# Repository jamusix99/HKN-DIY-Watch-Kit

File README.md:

# HKN Beta Psi DIY Watch Project
By: John Mentgen \
Init Date: 2026-02-16

## Directory Setup
 - **HW Design**: KiCad files for board setup
 - **SW**: Software Repo with details on how to compile

## Project Purpose
This project is meant to provide new ECEN students with a fun soldering project that members of IEEE and HKN Beta-Psi can help with and talk to students about possibilities in this field. The file holding the BOM details rough cost estimates for buying new parts from DigiKey and boards from JLCPCB.

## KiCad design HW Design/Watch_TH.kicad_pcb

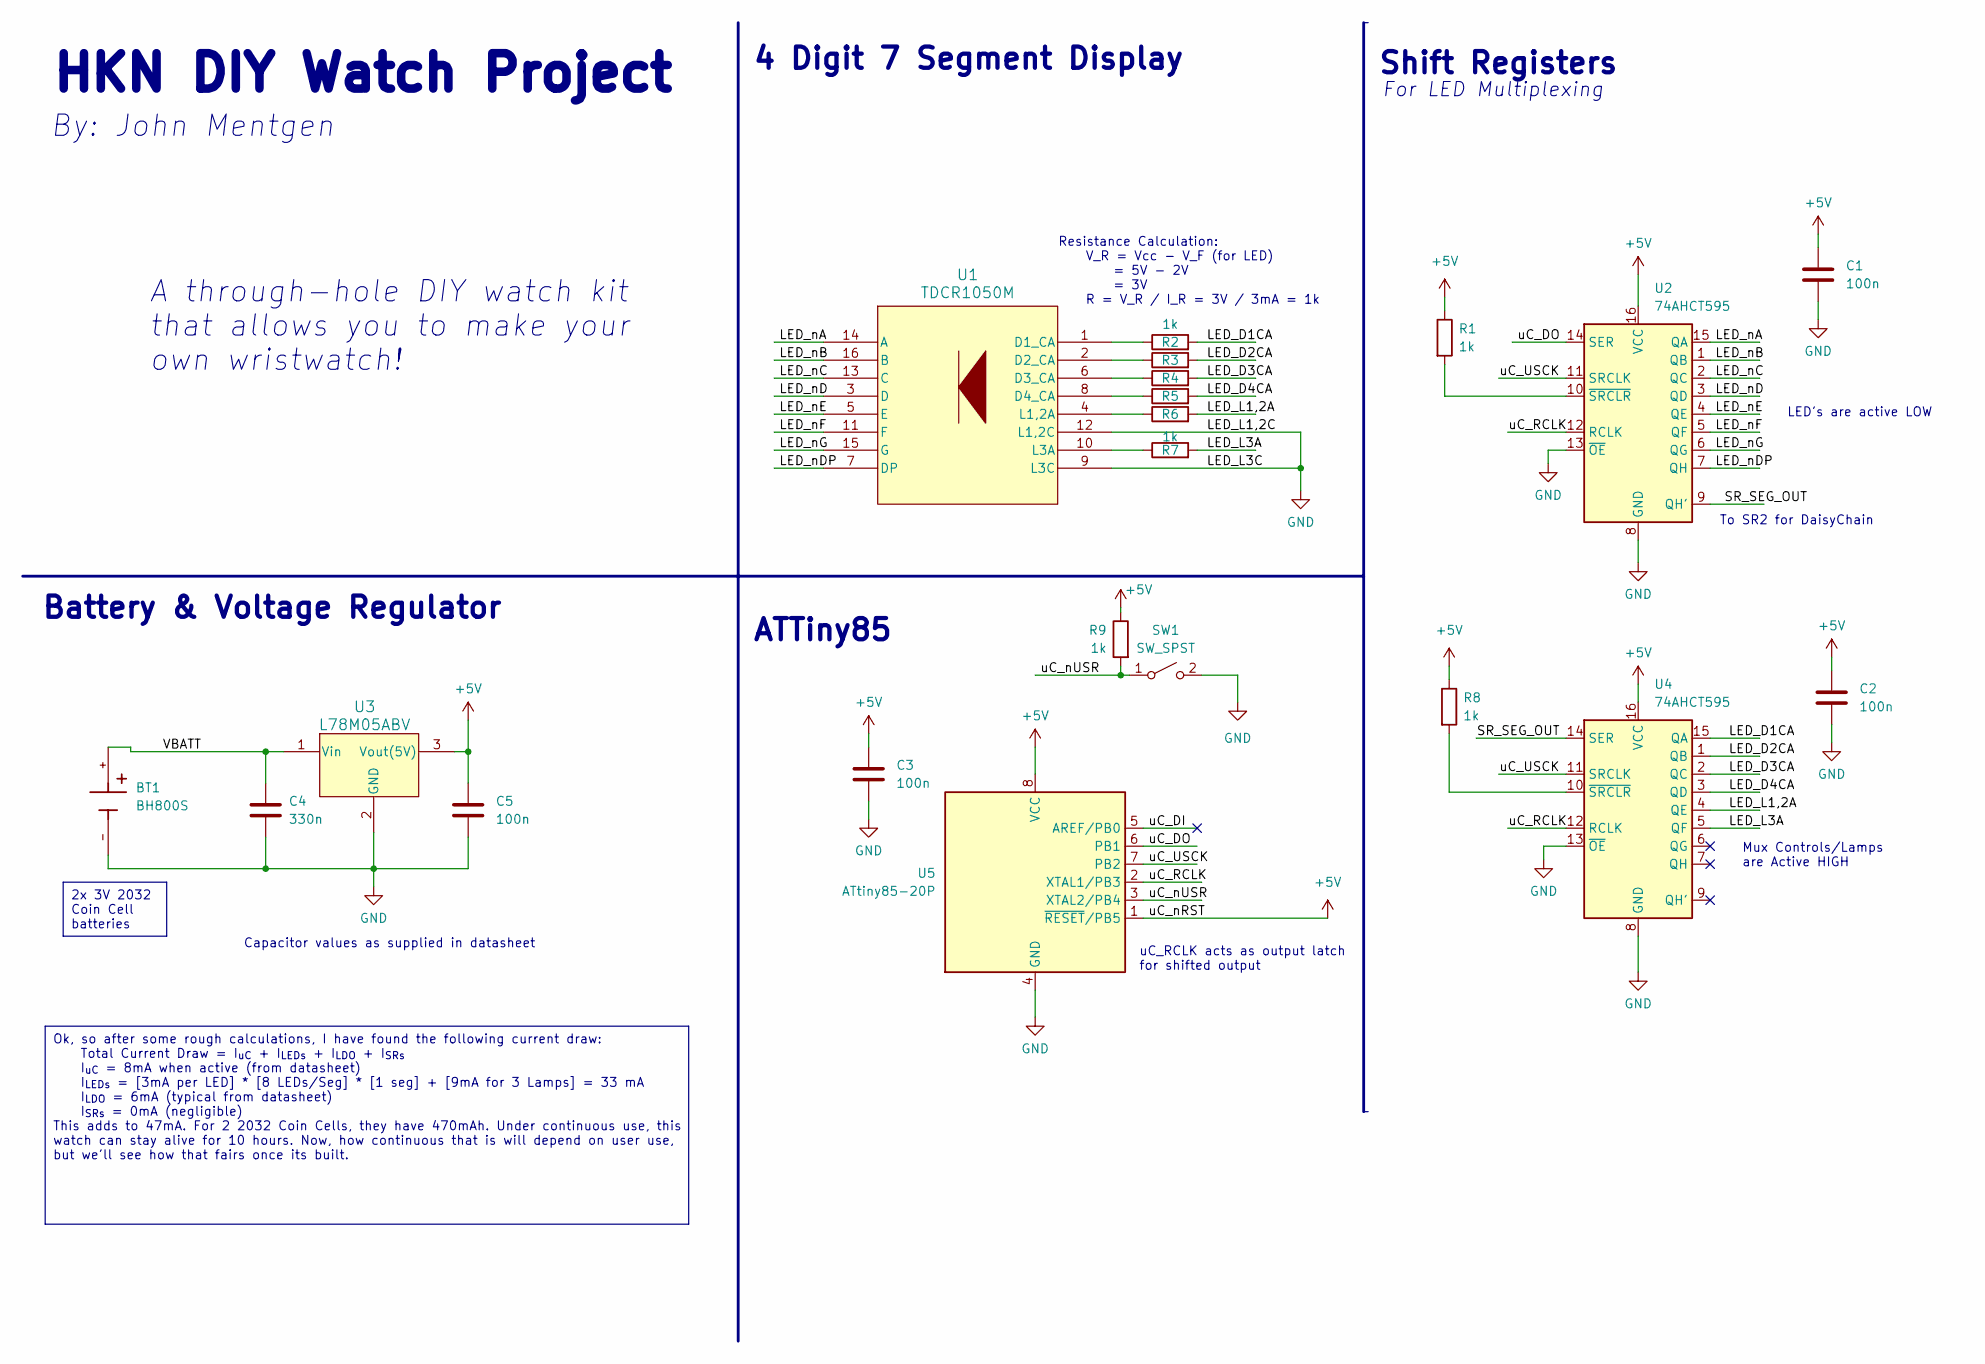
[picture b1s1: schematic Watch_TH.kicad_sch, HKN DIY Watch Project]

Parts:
BT1: BH800S; BAT_BH800S; PARTREV F
C1, C2, C3, C5: 100n; C_Rect_L4.0mm_W2.5mm_P2.50mm
C4: 330n; C_Radial_D6.3mm_H7.0mm_P2.50mm
R1, R2, R3, R4, R5, R6, R7, R8, R9: 1k; R_Axial_DIN0207_L6.3mm_D2.5mm_P10.16mm_Horizontal
SW1: SW_SPST; SW_PUSH_6mm
U1: TDCR1050M; TDCG1060M_VIS
U2, U4: 74AHCT595; DIP-16_W7.62mm
U3: L78M05ABV; TO-220_STM
U5: ATtiny85-20P; DIP-8_W7.62mm

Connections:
+5V: C1.1, C2.1, C3.1, C5.1, R1.1, R8.1, R9.1, U2.16 (VCC), U3.3 (Vout(5V)), U4.16 (VCC), U5.1 (~RESET/PB5), U5.8 (VCC)
/LED_D1CA: R2.2, U4.15 (QA)
/LED_D2CA: R3.2, U4.1 (QB)
/LED_D3CA: R4.2, U4.2 (QC)
/LED_D4CA: R5.2, U4.3 (QD)
/LED_L1,2A: R6.2, U4.4 (QE)
/LED_L3A: R7.2, U4.5 (QF)
/LED_nA: U1.14 (A), U2.15 (QA)
/LED_nB: U1.16 (B), U2.1 (QB)
/LED_nC: U1.13 (C), U2.2 (QC)
/LED_nD: U1.3 (D), U2.3 (QD)
/LED_nDP: U1.7 (DP), U2.7 (QH)
/LED_nE: U1.5 (E), U2.4 (QE)
/LED_nF: U1.11 (F), U2.5 (QF)
/LED_nG: U1.15 (G), U2.6 (QG)
/SR_SEG_OUT: U2.9 (QH'), U4.14 (SER)
/VBATT: BT1.+, C4.1, U3.1 (Vin)
/uC_DI: U5.5 (AREF/PB0)
/uC_DO: U2.14 (SER), U5.6 (PB1)
/uC_RCLK: U2.12 (RCLK), U4.12 (RCLK), U5.2 (XTAL1/PB3)
/uC_USCK: U2.11 (SRCLK), U4.11 (SRCLK), U5.7 (PB2)
/uC_nUSR: R9.2, SW1.1 (A), U5.3 (XTAL2/PB4)
GND: BT1.-, C1.2, C2.2, C3.2, C4.2, C5.2, SW1.2 (B), U1.9 (L3C), U1.12 (L1,2C), U2.8 (GND), U2.13 (~OE), U3.2 (GND), U4.8 (GND), U4.13 (~OE), U5.4 (GND)
unnamed: R2.1, U1.1 (D1_CA)
unnamed: R3.1, U1.2 (D2_CA)
unnamed: R4.1, U1.6 (D3_CA)
unnamed: R5.1, U1.8 (D4_CA)
unnamed: R6.1, U1.4 (L1,2A)
unnamed: R7.1, U1.10 (L3A)
unnamed: R1.2, U2.10 (~SRCLR)
unnamed: R8.2, U4.10 (~SRCLR)

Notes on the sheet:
Ok, so after some rough calculations, I have found the following current draw: Total Current Draw = I_{uC} + I_{LEDs} + I_{LDO} + I_{SRs} I_{uC} = 8mA when active (from datasheet) I_{LEDs} = [3mA per LED] * [8 LEDs/Seg] * [1 seg] + [9mA for 3 Lamps] = 33 mA I_{LDO} = 6mA (typical from datasheet) I_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
2x 3V 2032 Coin Cell batteries
uC_RCLK acts as output latch for shifted output
Battery & Voltage Regulator
Shift Registers
LED's are active LOW
For LED Multiplexing
A through-hole DIY watch kit that allows you to make your own wristwatch!
Mux Controls/Lamps are Active HIGH
Resistance Calculation: V_R = Vcc - V_F (for LED) = 5V - 2V = 3V R = V_R / I_R = 3V / 3mA = 1k
To SR2 for DaisyChain
HKN DIY Watch Project
By: John Mentgen
ATTiny85
4 Digit 7 Segment Display
Capacitor values as supplied in datasheet

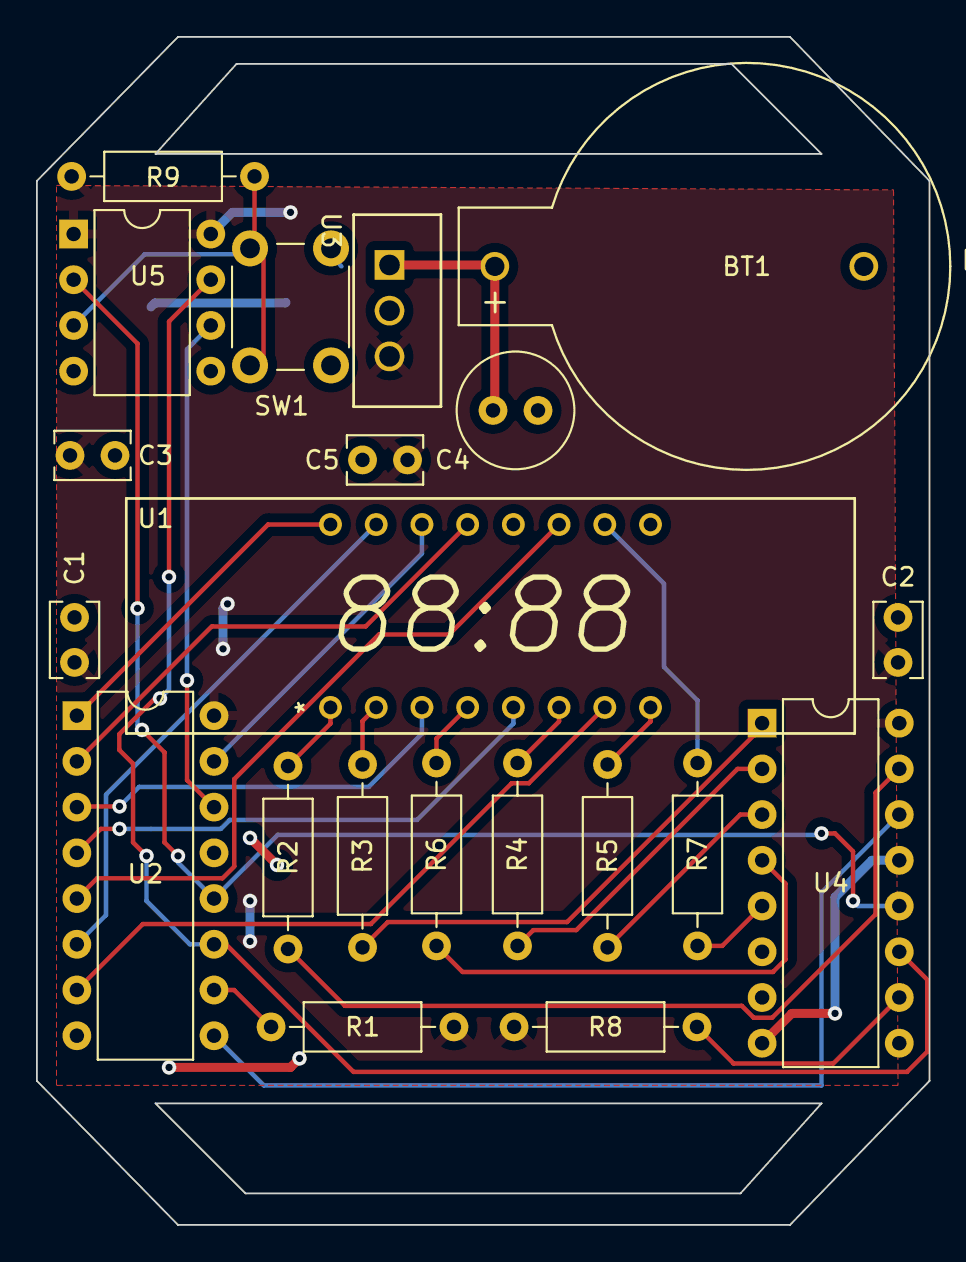
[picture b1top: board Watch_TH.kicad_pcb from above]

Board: 2 copper layers, 49.6 x 66.0 mm, 21 parts (0 on the bottom side), 30 nets.

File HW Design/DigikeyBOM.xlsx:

Digi-Key: Shopping Cart
Index | Quantity | Part Number | Manufacturer Part Number | Description | Customer Reference | Available | Backorder | Unit Price | Extended Price USD
1 | 1 | TDCR1050M-ND | TDCR1050M | DISP 7SEG 0.39" QUAD RED 16DIP |  | 1 | 0 | 3.48 | 3.48
2 | 1 | ATTINY85-20PU-ND | ATTINY85-20PU | IC MCU 8BIT 8KB FLASH 8DIP |  | 1 | 0 | 1.66 | 1.66
3 | 2 | 296-33695-5-ND | SN74AHCT595N | IC SR TRI-STATE 8BIT 16-PDIP |  | 2 | 0 | 0.9 | 1.8
4 | 1 | BH800S-ND | BH800S | BATT HLD COIN 20MM 2 CELL PC PIN |  | 1 | 0 | 1.35 | 1.35
5 | 2 | 5210-CR2032-ND | CR2032 | CR2032 20.0mn 3V Coin Cell |  | 2 | 0 | 0.57999999999999996 | 1.1599999999999999
6 | 1 | 478-TAP334K050CCS-ND | TAP334K050CCS | CAP TANT 0.33UF 10% 50V RADIAL |  | 1 | 0 | 0.6 | 0.6
7 | 4 | BC1084CT-ND | K104K15X7RF5TL2 | CAP CER 0.1UF 50V X7R RADIAL |  | 4 | 0 | 0.26 | 1.04
8 | 9 | CF18JT1K00CT-ND | CF18JT1K00 | RES 1K OHM 5% 1/8W AXIAL |  | 9 | 0 | 0.1 | 0.9
9 | 1 | SW402-ND | B3F-1020 | SWITCH TACTILE SPST-NO 0.05A 24V |  | 1 | 0 | 0.25 | 0.25
 |  |  |  |  |  |  | Price per kit: | 12.24
 |  |  |  |  |  |  | JLC Run (5x): | 25.75 | (+shipping)
 |  |  |  |  |  |  | JLC Run (25x): | 33.75 | (+shipping)
 |  |  |  |  |  |  | Proto run (x5): | 86.95
 |  |  |  |  |  |  | Prod run (x25): | 339.75

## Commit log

2026-02-17 Added README.md and SW directory
2026-02-19 HW Update
    Rerouted to connect missed ratsnest lines and connected together
    isolated pours
    Tags:
    * Type: BugFix
2026-02-19 Revise project title and description in README
    Updated project title and clarified the involvement of HKN Beta-Psi.
